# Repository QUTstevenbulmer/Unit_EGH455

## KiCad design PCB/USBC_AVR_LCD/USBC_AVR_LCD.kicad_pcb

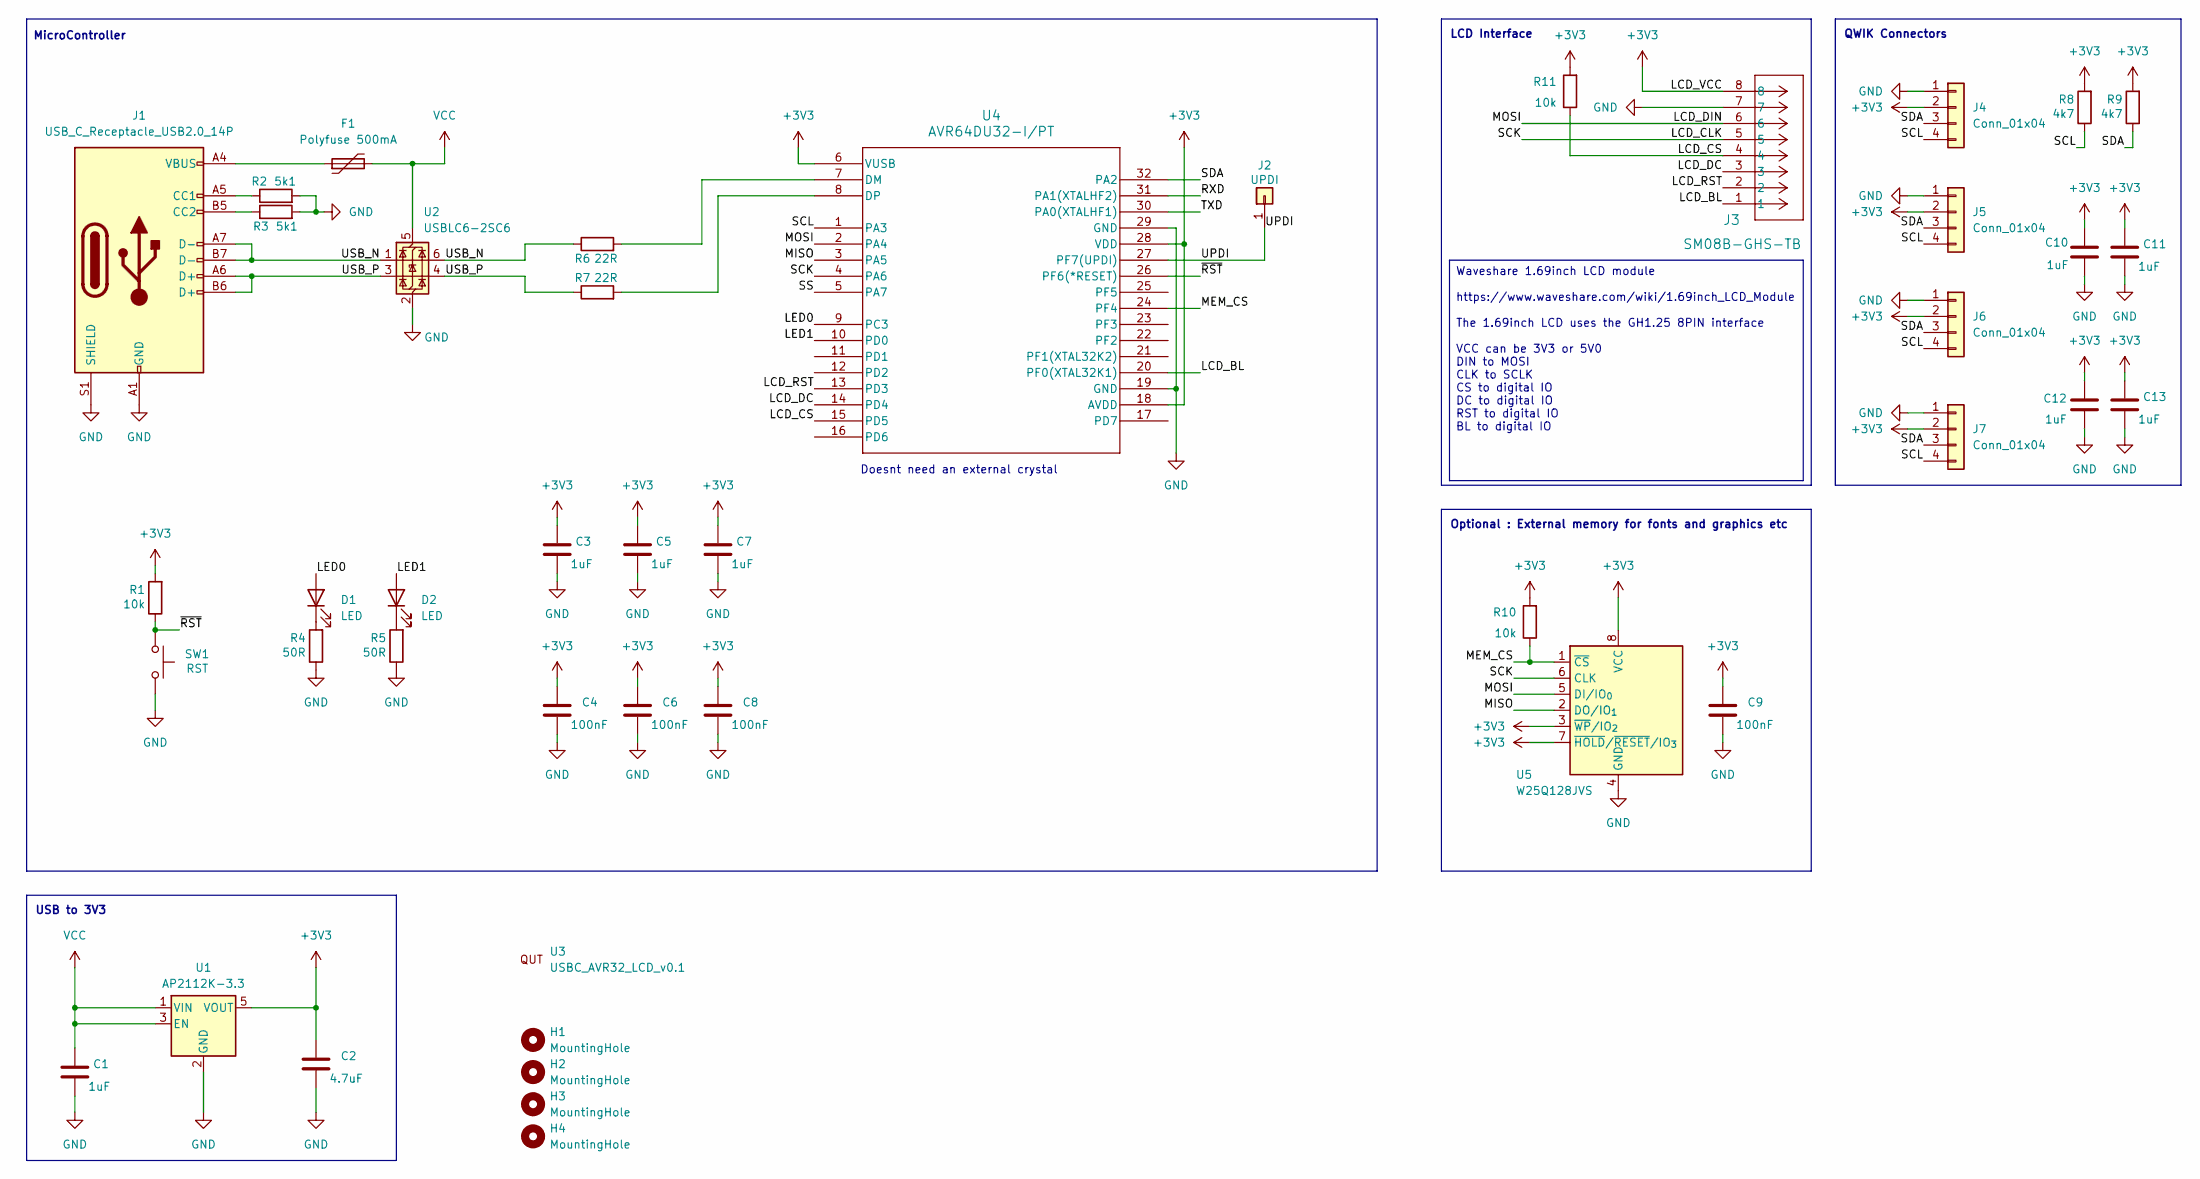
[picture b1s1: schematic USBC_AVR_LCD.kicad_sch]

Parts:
C1, C3, C5, C7, C10, C11, C12, C13: 1uF; C_0402_1005Metric_Pad0.74x0.62mm_HandSolder
C2: 4.7uF; C_0402_1005Metric_Pad0.74x0.62mm_HandSolder
C4, C6, C8, C9: 100nF; C_0402_1005Metric_Pad0.74x0.62mm_HandSolder
D1, D2: LED; LED_0603_1608Metric_Pad1.05x0.95mm_HandSolder
F1: Polyfuse 500mA; Fuse_0805_2012Metric_Pad1.15x1.40mm_HandSolder
H1, H2, H3, H4: MountingHole; MountingHole_2.2mm_M2
J1: USB_C_Receptacle_USB2.0_14P; USB_C_Receptacle_HRO_TYPE-C-31-M-12
J2: UPDI; PinHeader_1x01_P2.54mm_Vertical
J3: SM08B-GHS-TB; JST_GH_SM08B-GHS-TB_1x08-1MP_P1.25mm_Horizontal
J4, J5, J6, J7: Conn_01x04; JST_SH_SM04B-SRSS-TB_1x04-1MP_P1.00mm_Horizontal
R1, R10, R11: 10k; R_0402_1005Metric_Pad0.72x0.64mm_HandSolder
R2, R3: 5k1; R_0402_1005Metric_Pad0.72x0.64mm_HandSolder
R4, R5: 50R; R_0402_1005Metric_Pad0.72x0.64mm_HandSolder
R6, R7: 22R; R_0402_1005Metric_Pad0.72x0.64mm_HandSolder
R8, R9: 4k7; R_0402_1005Metric_Pad0.72x0.64mm_HandSolder
SW1: RST; Switch SMD STO
U1: AP2112K-3.3; SOT-23-5
U2: USBLC6-2SC6; SOT-23-6
U3: USBC_AVR32_LCD_v0.1; logo_QUT
U4: AVR64DU32-I/PT; TQFP32_PT_MCH
U5: W25Q128JVS; SOIC-8_5.3x5.3mm_P1.27mm

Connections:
+3V3: C2.1, C3.1, C4.1, C5.1, C6.1, C7.1, C8.1, C9.1, C10.1, C11.1, C12.1, C13.1, J3.8, J4.2, J5.2, J6.2, J7.2, R1.2, R8.2, R9.2, R10.2, R11.2, U1.5 (VOUT), U4.6 (VUSB), U4.18 (AVDD), U4.28 (VDD), U5.3 (~WP/IO_{2}), U5.7 (~HOLD/~RESET/IO_{3}), U5.8 (VCC)
/LCD_BL: J3.1, U4.20 (PF0(XTAL32K1))
/LCD_CLK: J3.5, U4.4 (PA6), U5.6 (CLK)
/LCD_CS: J3.4, R11.1, U4.15 (PD5)
/LCD_DC: J3.3, U4.14 (PD4)
/LCD_DIN: J3.6, U4.2 (PA4), U5.5 (DI/IO_{0})
/LCD_RST: J3.2, U4.13 (PD3)
/LED0: D1.2 (A), U4.9 (PC3)
/LED1: D2.2 (A), U4.10 (PD0)
/MEM_CS: R10.1, U4.24 (PF4), U5.1 (~CS)
/MISO: U4.3 (PA5), U5.2 (DO/IO_{1})
/RXD: U4.31 (PA1(XTALHF2))
/SCL: J4.4, J5.4, J6.4, J7.4, R8.1, U4.1 (PA3)
/SDA: J4.3, J5.3, J6.3, J7.3, R9.1, U4.32 (PA2)
/SS: U4.5 (PA7)
/TXD: U4.30 (PA0(XTALHF1))
/UPDI: J2.1 (Pin_1_1), U4.27 (PF7(UPDI))
/USB_N: J1.A7 (D-), J1.B7 (D-), R6.1, U2.1 (I/O1), U2.6 (I/O1)
/USB_P: J1.A6 (D+), J1.B6 (D+), R7.1, U2.3 (I/O2), U2.4 (I/O2)
/~RST: R1.1, SW1.1, U4.26 (PF6(*RESET))
GND: C1.2, C2.2, C3.2, C4.2, C5.2, C6.2, C7.2, C8.2, C9.2, C10.2, C11.2, C12.2, C13.2, J1.A1 (GND), J1.A12 (GND), J1.B1 (GND), J1.B12 (GND), J1.S1 (SHIELD), J3.7, J4.1, J5.1, J6.1, J7.1, R2.2, R3.2, R4.1, R5.1, SW1.2, U1.2 (GND), U2.2 (GND), U4.19 (GND), U4.29 (GND), U5.4 (GND)
unnamed: D1.1 (K), R4.2
unnamed: D2.1 (K), R5.2
unnamed: F1.1, J1.A4 (VBUS), J1.A9 (VBUS), J1.B4 (VBUS), J1.B9 (VBUS)
unnamed: J1.A5 (CC1), R2.1
unnamed: J1.B5 (CC2), R3.1
unnamed: R6.2, U4.7 (DM)
unnamed: R7.2, U4.8 (DP)
VCC: C1.1, F1.2, U1.1 (VIN), U1.3 (EN), U2.5 (VBUS)

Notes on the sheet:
USB to 3V3
MicroController
Optional : External memory for fonts and graphics etc
LCD Interface
Doesnt need an external crystal
QWIK Connectors
Waveshare 1.69inch LCD module https://www.waveshare.com/wiki/1.69inch_LCD_Module The 1.69inch LCD uses the GH1.25 8PIN interface VCC can be 3V3 or 5V0 DIN to MOSI CLK to SCLK CS to digital IO DC to digital IO RST to digital IO BL to digital IO

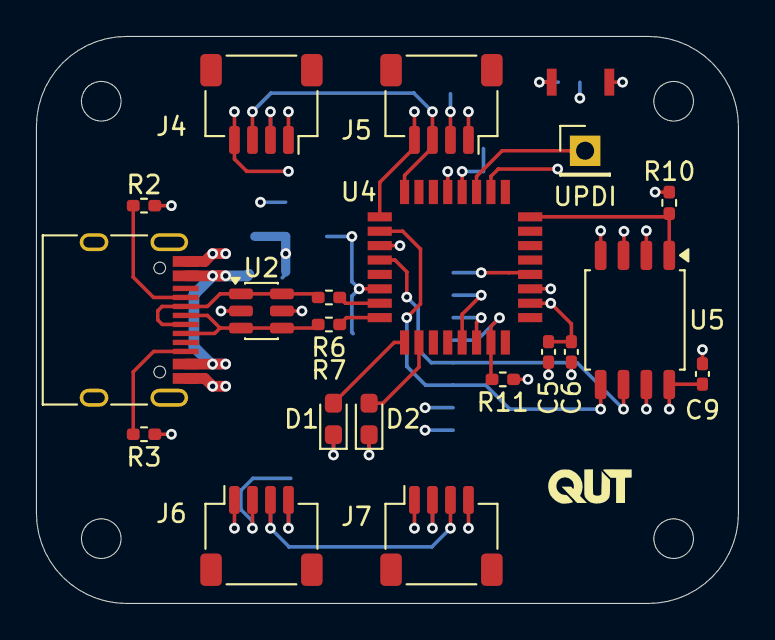
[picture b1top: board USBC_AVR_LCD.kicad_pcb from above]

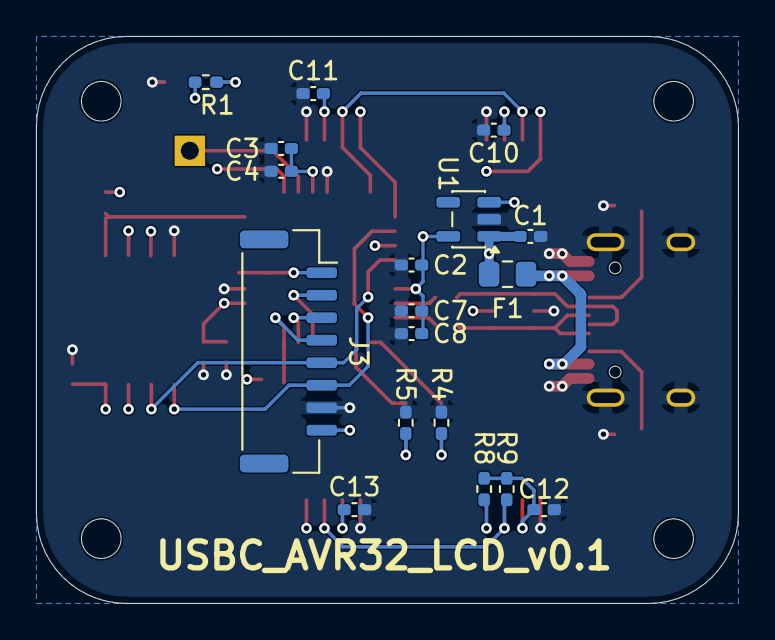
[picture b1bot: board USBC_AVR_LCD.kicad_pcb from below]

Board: 4 copper layers, 39.0 x 31.5 mm, 44 parts (18 on the bottom side), 26 nets.

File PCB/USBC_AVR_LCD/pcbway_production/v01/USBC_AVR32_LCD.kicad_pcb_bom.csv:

Designator,Quantity,Value,Footprint,Package,MPN,DNP,Mount_Type,Description,KiLib_Generator,PN_LCSC,PN_Digikey,Manufacturer,PN_Manufacturer,LCSC PN,Sim.Pins,MANUFACTURER
"C1, C10, C11, C12, C13, C3, C5, C7",8,1uF,C_0402_1005Metric_Pad0.74x0.62mm_HandSolder,,,,smt,Unpolarized capacitor,SMD_2terminal_chip_molded,C77009,490-10017-1-ND,Murata Electronics,GRM155R61E105KA12D,C77009,,
C2,1,4.7uF,C_0402_1005Metric_Pad0.74x0.62mm_HandSolder,,,,smt,Unpolarized capacitor,SMD_2terminal_chip_molded,C23733,1276-1482-1-ND,Samsung Electro-Mechanics,CL05A475MP5NRNC,C23733,,
"C4, C6, C8, C9",4,100nF,C_0402_1005Metric_Pad0.74x0.62mm_HandSolder,,,,smt,Unpolarized capacitor,SMD_2terminal_chip_molded,C105882,311-3342-1-ND,YAGEO,CC0402KRX5R9BB104,C105882,,
"D1, D2",2,LED,LED_0603_1608Metric_Pad1.05x0.95mm_HandSolder,,,,smt,3V2 20mA,SMD_2terminal_chip_molded,C497940,732-12013-1-ND,Würth Elektronik,150060BS55040,C497940,1=K 2=A,
F1,1,Polyfuse 500mA,Fuse_0805_2012Metric_Pad1.15x1.40mm_HandSolder,,,,smt,"Resettable fuse, polymeric positive temperature coefficient",SMD_2terminal_chip_molded,C207022,F2772CT-ND,,0805L050WR,,,Littelfuse
J1,1,USB_C_Receptacle_USB2.0_14P,USB_C_Receptacle_HRO_TYPE-C-31-M-12,,,,smt,USB 2.0-only 14P Type-C Receptacle connector,,C165948,,Korean Hroparts Elec,TYPE-C-31-M-12,C165948,,
J3,1,SM08B-GHS-TB,JST_GH_SM08B-GHS-TB_1x08-1MP_P1.25mm_Horizontal,,,,smt,,connector/SMD_single_row_plus_mounting_pad,,455-1570-1-ND,,SM08B-GHS-TB,,,
"J4, J5, J6, J7",4,Conn_01x04,JST_SH_SM04B-SRSS-TB_1x04-1MP_P1.00mm_Horizontal,,,,smt,"Generic connector, single row, 01x04, script generated (kicad-library-utils/schlib/autogen/connector/)",connector/SMD_single_row_plus_mounting_pad,,,,,,,
"R1, R10, R11",3,10k,R_0402_1005Metric_Pad0.72x0.64mm_HandSolder,,,,smt,,SMD_2terminal_chip_molded,"[R1]C851816; [R10,R11]C114765","[R1]YAG1249CT-ND; [R10,R11]311-22.0LRCT-ND",YAGEO,"[R1]RC0402FR-0710KP; [R10,R11]RC0402FR-0722RL","[R1]C851816; [R10,R11]C114765",,
"R2, R3",2,5k1,R_0402_1005Metric_Pad0.72x0.64mm_HandSolder,,,,smt,,C212346,C105872,311-5.10KLRCT-ND,YAGEO,RC0402FR-075K1L,C105872,,
"R4, R5",2,150R,R_0402_1005Metric_Pad0.72x0.64mm_HandSolder,,,,smt,,SMD_2terminal_chip_molded,C4258677,13-RC0402FR-13150RLCT-ND,YAGEO,RC0402FR-13150RL,C4258677,,
"R6, R7",2,22R,R_0402_1005Metric_Pad0.72x0.64mm_HandSolder,,,,smt,,SMD_2terminal_chip_molded,C114765,311-22.0LRCT-ND,YAGEO,RC0402FR-0722RL,C114765,,
"R8, R9",2,4k7,R_0402_1005Metric_Pad0.72x0.64mm_HandSolder,,,,smt,,SMD_2terminal_chip_molded,C105870,311-4.7KJRCT-ND,,,C105870,,
SW1,1,RST,Switch SMD STO,,,,smt,,,C25168823,2508-R-667995CT-ND,Mitsumi,R-667995,C25168823,,
U1,1,AP2112K-3.3,SOT-23-5,,,,smt,"600mA low dropout linear regulator, with enable pin, 3.8V-6V input voltage range, 3.3V fixed positive output, SOT-23-5",package/gullwing,,,,,,,
U2,1,USBLC6-2SC6,SOT-23-6,,,,smt,"Very low capacitance ESD protection diode, 2 data-line, SOT-23-6",package/gullwing,C7519,497-5235-1-ND,,USBLC6-2SC6,,,STMicroelectronics
U3,1,USBC_AVR32_LCD_v0.1,logo_QUT,,,,tht,,,,,,,,,
U4,1,AVR64DU32-I/PT,TQFP32_PT_MCH,,,,smt,,,,150-AVR64DU32-I/PT-ND,Microchip Technology,AVR64DU32-I/PT,,,
U5,1,W25Q128JVS,SOIC-8_5.3x5.3mm_P1.27mm,,,,smt,"128Mbit / 16MiB Serial Flash Memory, Standard/Dual/Quad SPI, 2.7-3.6V, SOIC-8",package/gullwing,,256-W25Q128JVSIMTRCT-ND,Winbond Electronics,W25Q128JVSIM TR,,,
